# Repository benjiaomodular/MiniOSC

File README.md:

# MiniOSC
[![CC BY-SA 4.0][cc-by-sa-shield]][cc-by-sa]

## Schematics
**Version 2.1**

More info on my website: https://benjiaomodular.com/post/2024-09-20-miniosc-v2/

## PCBs
This project was sponsored by PCBWay. You can order the boards from them directly!
1. [MiniOSC v2.1 - Front panel](https://www.pcbway.com/project/shareproject/_1_of_2_MiniOSC_v2_1_Front_Panel_4b8c5ae8.html) 
2. [MiniOSC v2.1 - Main board](https://www.pcbway.com/project/shareproject/_2_of_2_MiniOSC_v2_1_Main_Board_2ed4e925.html)

You can also download my files from https://github.com/benjiaomodular/MiniOSC/blob/main/fabrication/

## Old versions

**Version 1.1**

More info on my website: https://benjiaomodular.com/post/2021-12-03-volt-per-octave-40106-vco/

## License

This work is licensed under a
[Creative Commons Attribution-ShareAlike 4.0 International License][cc-by-sa].

[![CC BY-SA 4.0][cc-by-sa-image]][cc-by-sa]

[cc-by-sa]: http://creativecommons.org/licenses/by-sa/4.0/
[cc-by-sa-image]: https://licensebuttons.net/l/by-sa/4.0/88x31.png
[cc-by-sa-shield]: https://img.shields.io/badge/License-CC%20BY--SA%204.0-lightgrey.svg

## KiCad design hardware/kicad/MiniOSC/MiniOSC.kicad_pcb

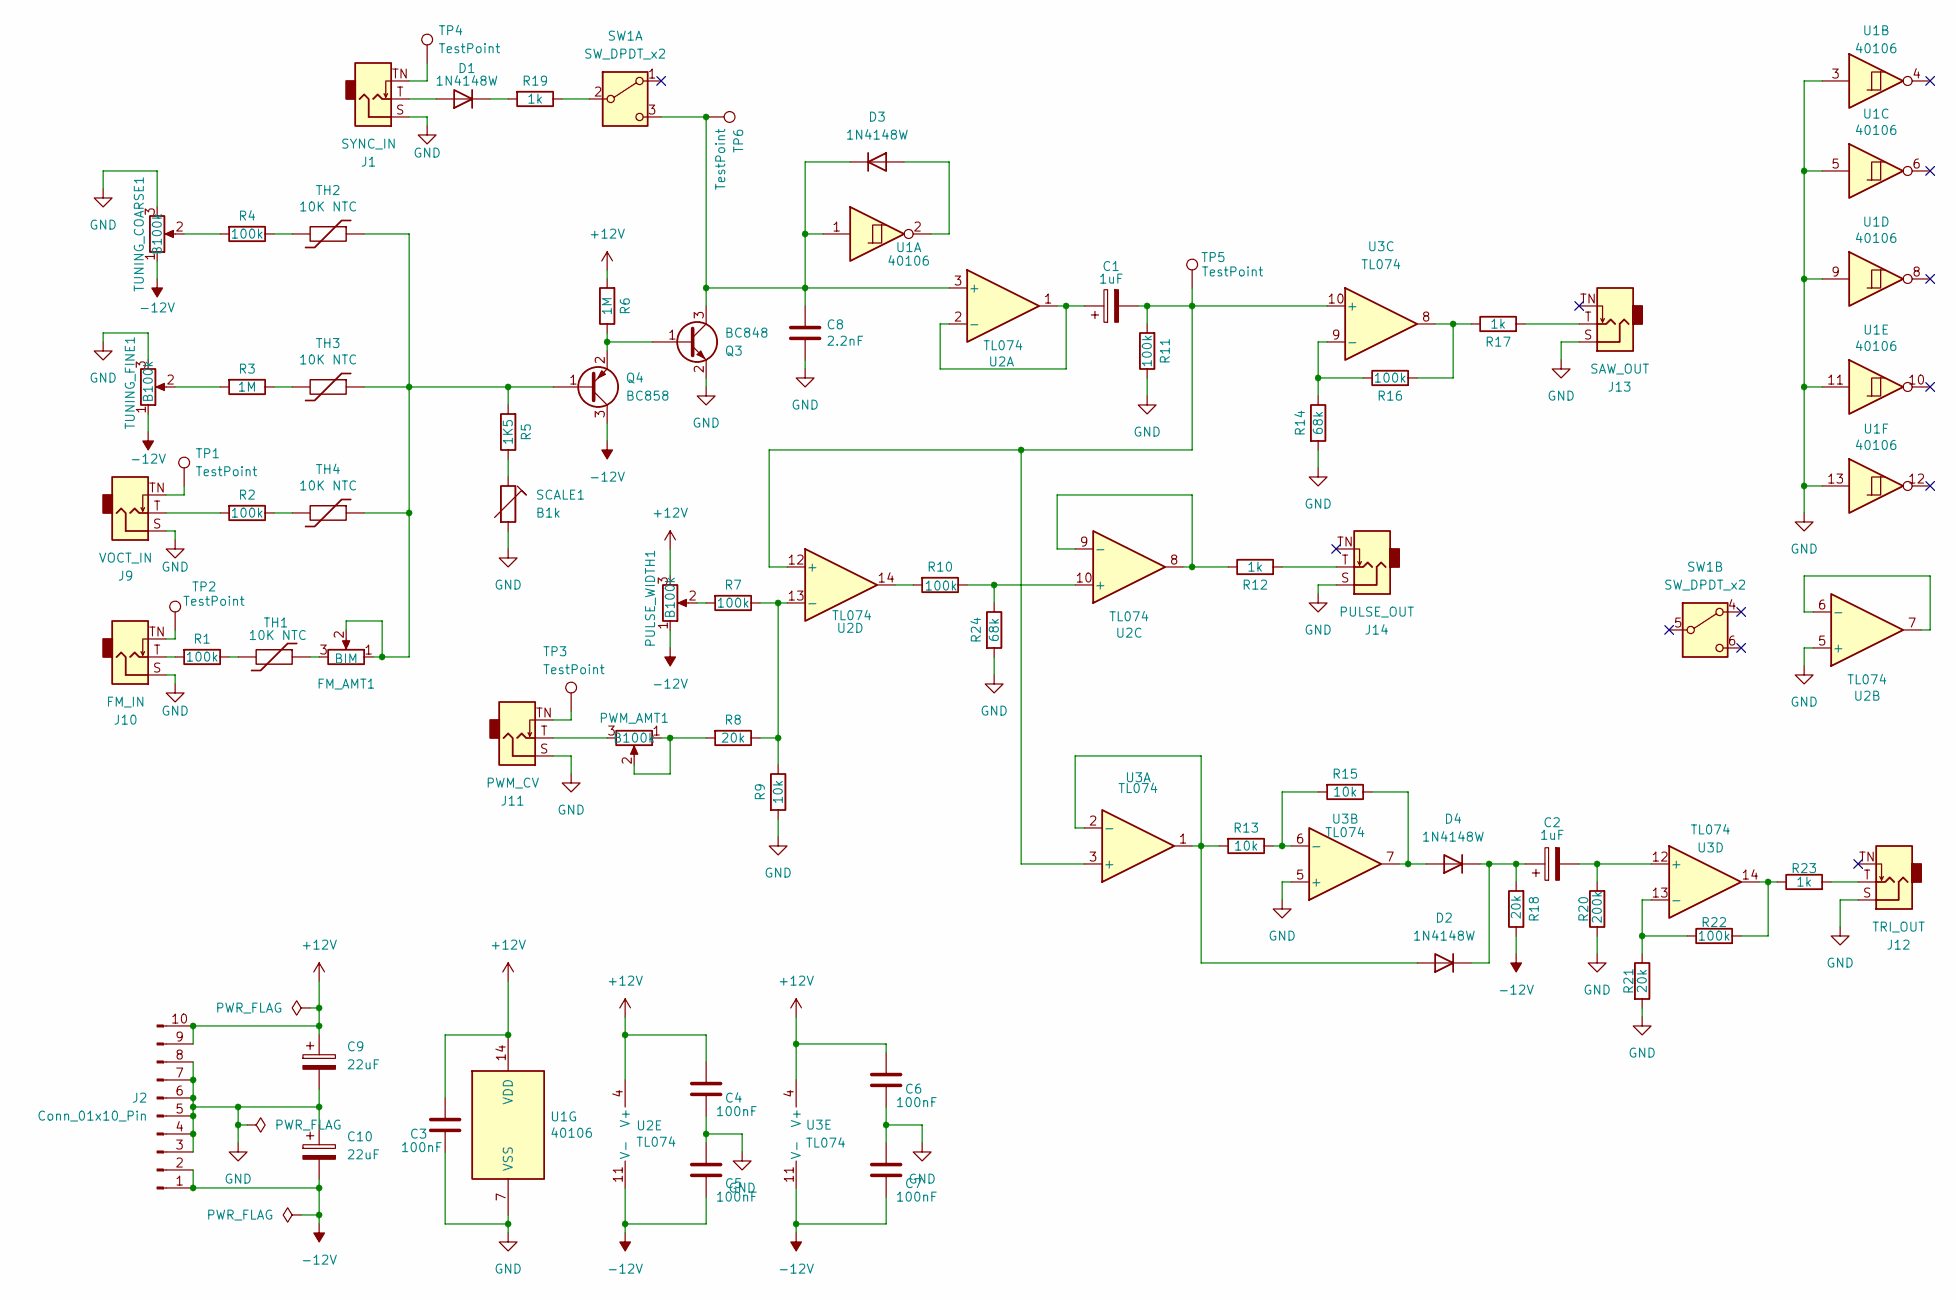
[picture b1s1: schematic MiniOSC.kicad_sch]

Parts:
C1, C2: 1uF; C_0805_2012Metric_Pad1.18x1.45mm_HandSolder; Part # UMK107AB7105KA-T
C3, C4, C5, C6, C7: 100nF; C_0805_2012Metric_Pad1.18x1.45mm_HandSolder; Part # CC0603JRX7R9BB104
C8: 2.2nF; C_0603_1608Metric_Pad1.08x0.95mm_HandSolder; Part # VJ0603Y681KXAAC
C9, C10: 22uF; CP_Elec_4x5.8; Part # EEE-FT1V220AR
D1, D2, D3, D4: 1N4148W; D_SOD-123; Part # 1N4148W_R2_00001
FM_AMT1: BIM; Potentiometer_RV09; Part # RV09AF-40-20K-B1M
J1: SYNC_IN; AudioJack_3.5mm; Part # PJ-3001F 3.5mm Mono Phone Jack
J2: Conn_01x10_Pin; Header_IDC2x05_NoArrow; Part # X9555WV-2X05-6TV01
J9: VOCT_IN; AudioJack_3.5mm; Part # PJ-3001F 3.5mm Mono Phone Jack
J10: FM_IN; AudioJack_3.5mm; Part # PJ-3001F 3.5mm Mono Phone Jack
J11: PWM_CV; AudioJack_3.5mm; Part # PJ-3001F 3.5mm Mono Phone Jack
J12: TRI_OUT; AudioJack_3.5mm; Part # PJ-3001F 3.5mm Mono Phone Jack
J13: SAW_OUT; AudioJack_3.5mm; Part # PJ-3001F 3.5mm Mono Phone Jack
J14: PULSE_OUT; AudioJack_3.5mm; Part # PJ-3001F 3.5mm Mono Phone Jack
PULSE_WIDTH1: B100k; Potentiometer_RV09; Part # RV9312NO-OS15A00-B100K-060
PWM_AMT1: B100k; Potentiometer_RV09; Part # RV09AF-40-20K-B100K
Q3: BC848; SOT-23; Part # BC848ALT1G
Q4: BC858; SOT-23; Part # BC858CLT3G
R1, R2, R4, R7, R10, R11, R16, R22: 100k; R_0603_1608Metric_Pad0.98x0.95mm_HandSolder; Part # RC0603FR-07100KL
R3, R6: 1M; R_0603_1608Metric_Pad0.98x0.95mm_HandSolder; Part # RC0603FR-071ML
R5: 1K5; R_0603_1608Metric_Pad0.98x0.95mm_HandSolder; Part # RC0603FR-071K5L
R8, R18: 20k; R_0603_1608Metric_Pad0.98x0.95mm_HandSolder; Part # RC0603FR-0720KL
R9, R13, R15: 10k; R_0603_1608Metric_Pad0.98x0.95mm_HandSolder; Part # AC0603FR-0710KL
R12, R17, R19, R23: 1k; R_0603_1608Metric_Pad0.98x0.95mm_HandSolder; Part # RC0603FR-071KL
R14, R24: 68k; R_0603_1608Metric_Pad0.98x0.95mm_HandSolder; Part # RC0603FR-0768KL
R20: 200k; R_0603_1608Metric_Pad0.98x0.95mm_HandSolder; Part # CR0603-FX-2003ELF
R21: 20k; R_0603_1608Metric_Pad0.98x0.95mm_HandSolder; Part # AC0603FR-0710KL
SCALE1: B1k; Potentiometer_Bourns_3296W_Vertical; Part # 3296W-1-102LF
SW1: SW_DPDT_x2; Button_KFC7x7; Part # PB-22E27-ROHS
TH1, TH2, TH3, TH4: 10K NTC; R_0805_2012Metric_Pad1.20x1.40mm_HandSolder; Part # NTCS0603E3103JLT
TP1, TP2, TP3, TP4, TP5, TP6: TestPoint; SolderWirePad_1x01_SMD_1x2mm
TUNING_COARSE1: B100k; Potentiometer_RV09; Part # RV9312NO-OS15A00-B100K-060
TUNING_FINE1: B100k; Potentiometer_RV09; Part # RV09AF-40-20K-B100K
U1: 40106; SOIC-14_3.9x8.7mm_P1.27mm; Part # CD40106BM96G4
U2, U3: TL074; SOIC-14_3.9x8.7mm_P1.27mm; Part # TL074ACDT

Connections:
+12V: C3.1, C4.1, C6.1, C9.1, J2.9, J2.10, PULSE_WIDTH1.3, R6.2, U1.14 (VDD), U2.4 (V+), U3.4 (V+)
-12V: C5.2, C7.2, C10.2, J2.1, J2.2, PULSE_WIDTH1.1, Q4.3 (C), R18.1, TUNING_COARSE1.1, TUNING_FINE1.1, U2.11 (V-), U3.11 (V-)
GND: C3.2, C4.2, C5.1, C6.2, C7.1, C8.2, C9.2, C10.1, J1.S, J2.3, J2.4, J2.5, J2.6, J2.7, J2.8, J9.S, J10.S, J11.S, J12.S, J13.S, J14.S, Q3.2 (E), R9.2, R11.1, R14.2, R20.1, R21.2, R24.2, SCALE1.2, TUNING_COARSE1.3, TUNING_FINE1.3, U1.3, U1.5, U1.7 (VSS), U1.9, U1.11, U1.13, U2.5 (+), U3.5 (+)
unnamed: D1.2 (A), J1.T
unnamed: D1.1 (K), R19.2
unnamed: D2.2 (A), R13.2, U3.1, U3.2 (-)
unnamed: C2.1, D2.1 (K), D4.1 (K), R18.2
unnamed: D3.2 (A), U1.2
unnamed: C8.1, D3.1 (K), Q3.3 (C), SW1.3 (C), TP6.1, U1.1, U2.3 (+)
unnamed: D4.2 (A), R15.1, U3.7
unnamed: FM_AMT1.3, TH1.1
unnamed: J1.TN, TP4.1
unnamed: J9.T, R2.2
unnamed: J9.TN, TP1.1
unnamed: J10.T, R1.2
unnamed: J10.TN, TP2.1
unnamed: J11.T, PWM_AMT1.3
unnamed: J11.TN, TP3.1
unnamed: J12.T, R23.2
unnamed: J13.T, R17.2
unnamed: J14.T, R12.2
unnamed: PULSE_WIDTH1.2, R7.2
unnamed: PWM_AMT1.1, PWM_AMT1.2, R8.2
unnamed: Q3.1 (B), Q4.2 (E), R6.1
unnamed: FM_AMT1.1, FM_AMT1.2, Q4.1 (B), R5.2, TH2.1, TH3.1, TH4.1
unnamed: R1.1, TH1.2
unnamed: R2.1, TH4.2
unnamed: R3.1, TH3.2
unnamed: R3.2, TUNING_FINE1.2
unnamed: R4.1, TH2.2
unnamed: R4.2, TUNING_COARSE1.2
unnamed: R5.1, SCALE1.1
unnamed: R10.2, U2.14
unnamed: R16.2, R17.1, U3.8
unnamed: R22.2, R23.1, U3.14
unnamed: R19.1, SW1.2 (B)
unnamed: C1.1, U2.1, U2.2 (-)
unnamed: U2.6 (-), U2.7
unnamed: R10.1, R24.1, U2.10 (+)
unnamed: R12.1, U2.8, U2.9 (-)
unnamed: C1.2, R11.2, TP5.1, U2.12 (+), U3.3 (+), U3.10 (+)
unnamed: R7.1, R8.1, R9.1, U2.13 (-)
unnamed: R13.1, R15.2, U3.6 (-)
unnamed: R14.1, R16.1, U3.9 (-)
unnamed: C2.2, R20.2, U3.12 (+)
unnamed: R21.1, R22.1, U3.13 (-)

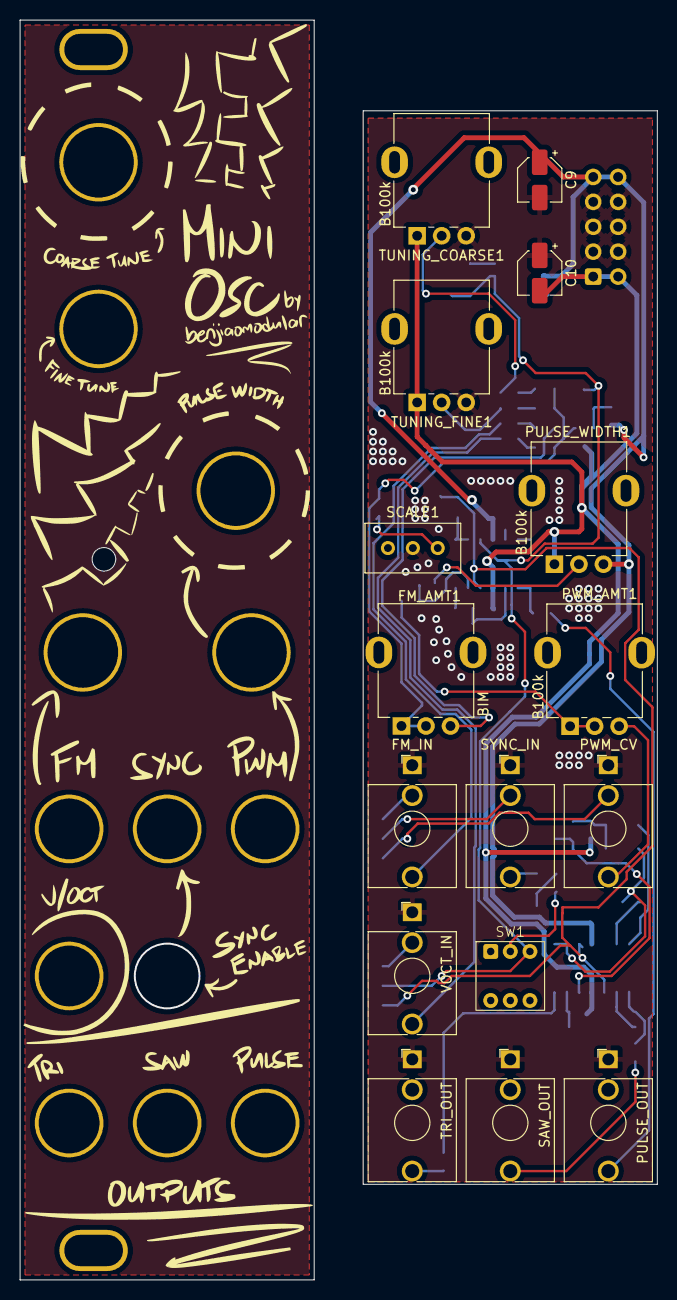
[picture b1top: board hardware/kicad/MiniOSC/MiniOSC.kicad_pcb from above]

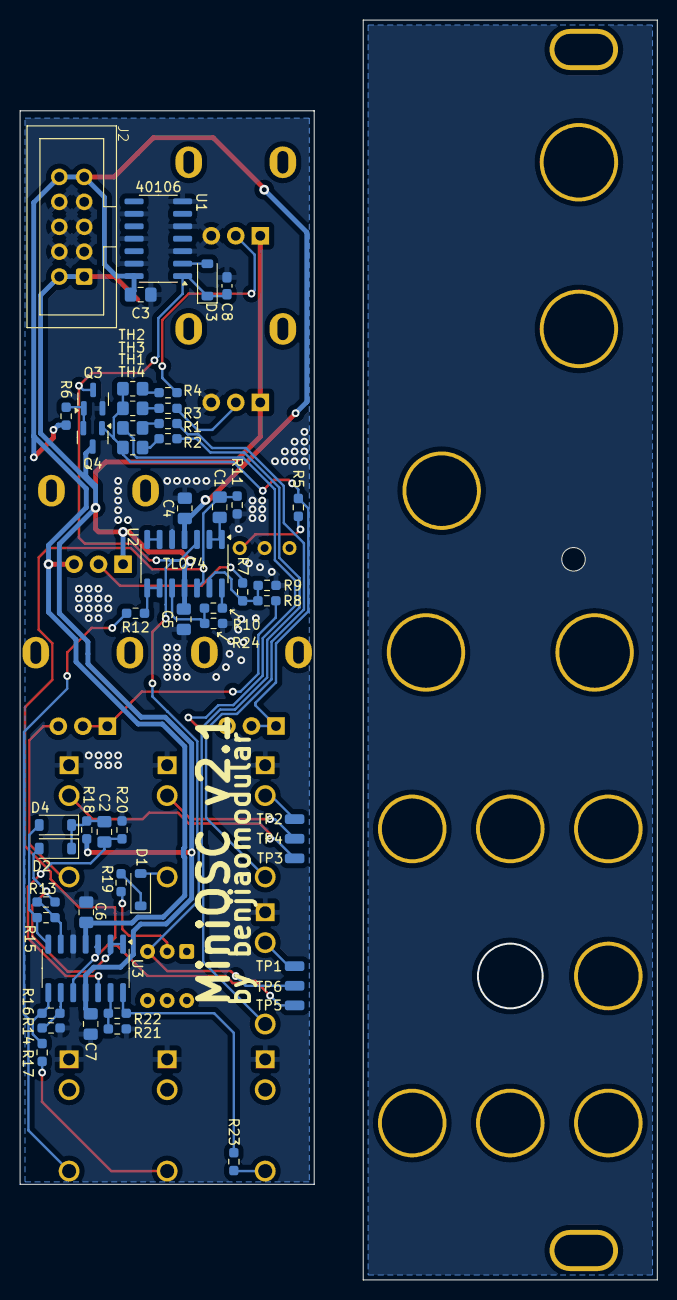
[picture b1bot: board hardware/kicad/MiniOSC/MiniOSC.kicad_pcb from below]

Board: 2 copper layers, 30.0 x 109.5 mm, 68 parts (52 on the bottom side), 46 nets.

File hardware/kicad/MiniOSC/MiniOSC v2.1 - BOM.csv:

"null","Sourced","Placed","References","Value","Footprint","URL","Manufacturer","Part #","Quantity"
1,"","","C3, C4, C5, C6, C7","100nF","C_0805_2012Metric_Pad1.18x1.45mm_HandSolder","https://mou.sr/4ekMsbM","YAGEO","CC0603JRX7R9BB104",5
2,"","","C1, C2","1uF","C_0805_2012Metric_Pad1.18x1.45mm_HandSolder","https://mou.sr/3XEhBl3","TAIYO YUDEN","UMK107AB7105KA-T",2
3,"","","C9, C10","22uF","CP_Elec_4x5.8","https://mou.sr/4ekMqRc","Panasonic","EEE-FT1V220AR",2
4,"","","C8","680pF","C_0603_1608Metric_Pad1.08x0.95mm_HandSolder","https://mou.sr/4goVMgC","Vishay / Vitramon","VJ0603Y681KXAAC",1
5,"","","R1, R2, R4, R7, R10, R11, R16, R22","100k","R_0603_1608Metric_Pad0.98x0.95mm_HandSolder","https://mou.sr/4el3qXS","YAGEO","RC0603FR-07100KL",8
6,"","","R12, R17, R19, R23","1k","R_0603_1608Metric_Pad0.98x0.95mm_HandSolder","https://mou.sr/3MKtPCB","YAGEO","RC0603FR-071KL",4
7,"","","R9, R13, R15","10k","R_0603_1608Metric_Pad0.98x0.95mm_HandSolder","https://mou.sr/3MINYsI","YAGEO","AC0603FR-0710KL",3
8,"","","R3, R6","1M","R_0603_1608Metric_Pad0.98x0.95mm_HandSolder","https://mou.sr/3Znalvs","YAGEO","RC0603FR-071ML",2
9,"","","R8, R18","20k","R_0603_1608Metric_Pad0.98x0.95mm_HandSolder","https://mou.sr/3z5b9KJ","YAGEO","RC0603FR-0720KL",2
10,"","","R14, R24","68k","R_0603_1608Metric_Pad0.98x0.95mm_HandSolder","https://mou.sr/3ToI2ZD","YAGEO","RC0603FR-0768KL",2
11,"","","R5","1K5","R_0603_1608Metric_Pad0.98x0.95mm_HandSolder","https://mou.sr/3zoxpz1","YAGEO"," RC0603FR-071K5L",1
12,"","","R20","200k","R_0603_1608Metric_Pad0.98x0.95mm_HandSolder","https://mou.sr/3XFl5np","Bourns","CR0603-FX-2003ELF",1
13,"","","R21","20k","R_0603_1608Metric_Pad0.98x0.95mm_HandSolder","https://mou.sr/3MINYsI","YAGEO","AC0603FR-0710KL",1
14,"","","D1, D2, D3, D4","1N4148W","D_SOD-123","https://mou.sr/3XEhTbD","Panjit"," 1N4148W_R2_00001",4
15,"","","U2, U3","TL074","SOIC-14_3.9x8.7mm_P1.27mm","https://mou.sr/3z6QVAe","STMicroelectronics","TL074ACDT",2
16,"","","U1",40106,"SOIC-14_3.9x8.7mm_P1.27mm","https://mou.sr/47m5xIo","Texas Instruments","CD40106BM96G4",1
17,"","","SW1","SW_DPDT_x2","Button_KFC7x7","https://www.taydaelectronics.com/push-button-switch-dc-30v-0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","DAIER"," PB-22E27-ROHS",1
18,"","","TH1, TH2, TH3, TH4","10K NTC","R_0805_2012Metric_Pad1.20x1.40mm_HandSolder","https://mou.sr/4el3hDO","Vishay / BC Components","NTCS0603E3103JLT",4
19,"","","PULSE_WIDTH1, TUNING_COARSE1","B100k","Potentiometer_RV09","https://www.taydaelectronics.com/tayda-100k-ohm-linear-taper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","Tayda Electronics","RV9312NO-OS15A00-B100K-060",2
20,"","","PWM_AMT1, TUNING_FINE1","B100k","Potentiometer_RV09","https://www.taydaelectronics.com/100k-ohm-linear-taper-poten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","ALPHA","RV09AF-40-20K-B100K",2
21,"","","FM_AMT1","BIM","Potentiometer_RV09","https://www.taydaelectronics.com/1m-ohm-linear-taper-potenti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","ALPHA","RV09AF-40-20K-B1M",1
22,"","","Q3","BC848","SOT-23","https://mou.sr/3B2EAO3","onsemi","BC848ALT1G",1
23,"","","Q4","BC858","SOT-23","https://mou.sr/3ZkYkq0","onsemi","BC858CLT3G",1
24,"","","SCALE1","B1k","Potentiometer_Bourns_3296W_Vertical","https://www.taydaelectronics.com/1k-ohm-trimmer-potentiomete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","ALPHA","3296W-1-102LF",1
25,"","","J1","SYNC_IN","AudioJack_3.5mm","https://www.taydaelectronics.com/pj-3001f-3-5-mm-mono-phone-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","Tayda Electronics","PJ-3001F 3.5mm Mono Phone Jack",1
26,"","","J2","Conn_01x10_Pin","Header_IDC2x05_NoArrow","","XKB Connectivity","X9555WV-2X05-6TV01",1
27,"","","J9","VOCT_IN","AudioJack_3.5mm","https://www.taydaelectronics.com/pj-3001f-3-5-mm-mono-phone-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","Tayda Electronics","PJ-3001F 3.5mm Mono Phone Jack",1
28,"","","J10","FM_IN","AudioJack_3.5mm","https://www.taydaelectronics.com/pj-3001f-3-5-mm-mono-phone-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","Tayda Electronics","PJ-3001F 3.5mm Mono Phone Jack",1
29,"","","J11","PWM_CV","AudioJack_3.5mm","https://www.taydaelectronics.com/pj-3001f-3-5-mm-mono-phone-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","Tayda Electronics","PJ-3001F 3.5mm Mono Phone Jack",1
30,"","","J12","TRI_OUT","AudioJack_3.5mm","https://www.taydaelectronics.com/pj-3001f-3-5-mm-mono-phone-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","Tayda Electronics","PJ-3001F 3.5mm Mono Phone Jack",1
31,"","","J13","SAW_OUT","AudioJack_3.5mm","https://www.taydaelectronics.com/pj-3001f-3-5-mm-mono-phone-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","Tayda Electronics","PJ-3001F 3.5mm Mono Phone Jack",1
32,"","","J14","PULSE_OUT","AudioJack_3.5mm","https://www.taydaelectronics.com/pj-3001f-3-5-mm-mono-phone-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","Tayda Electronics","PJ-3001F 3.5mm Mono Phone Jack",1

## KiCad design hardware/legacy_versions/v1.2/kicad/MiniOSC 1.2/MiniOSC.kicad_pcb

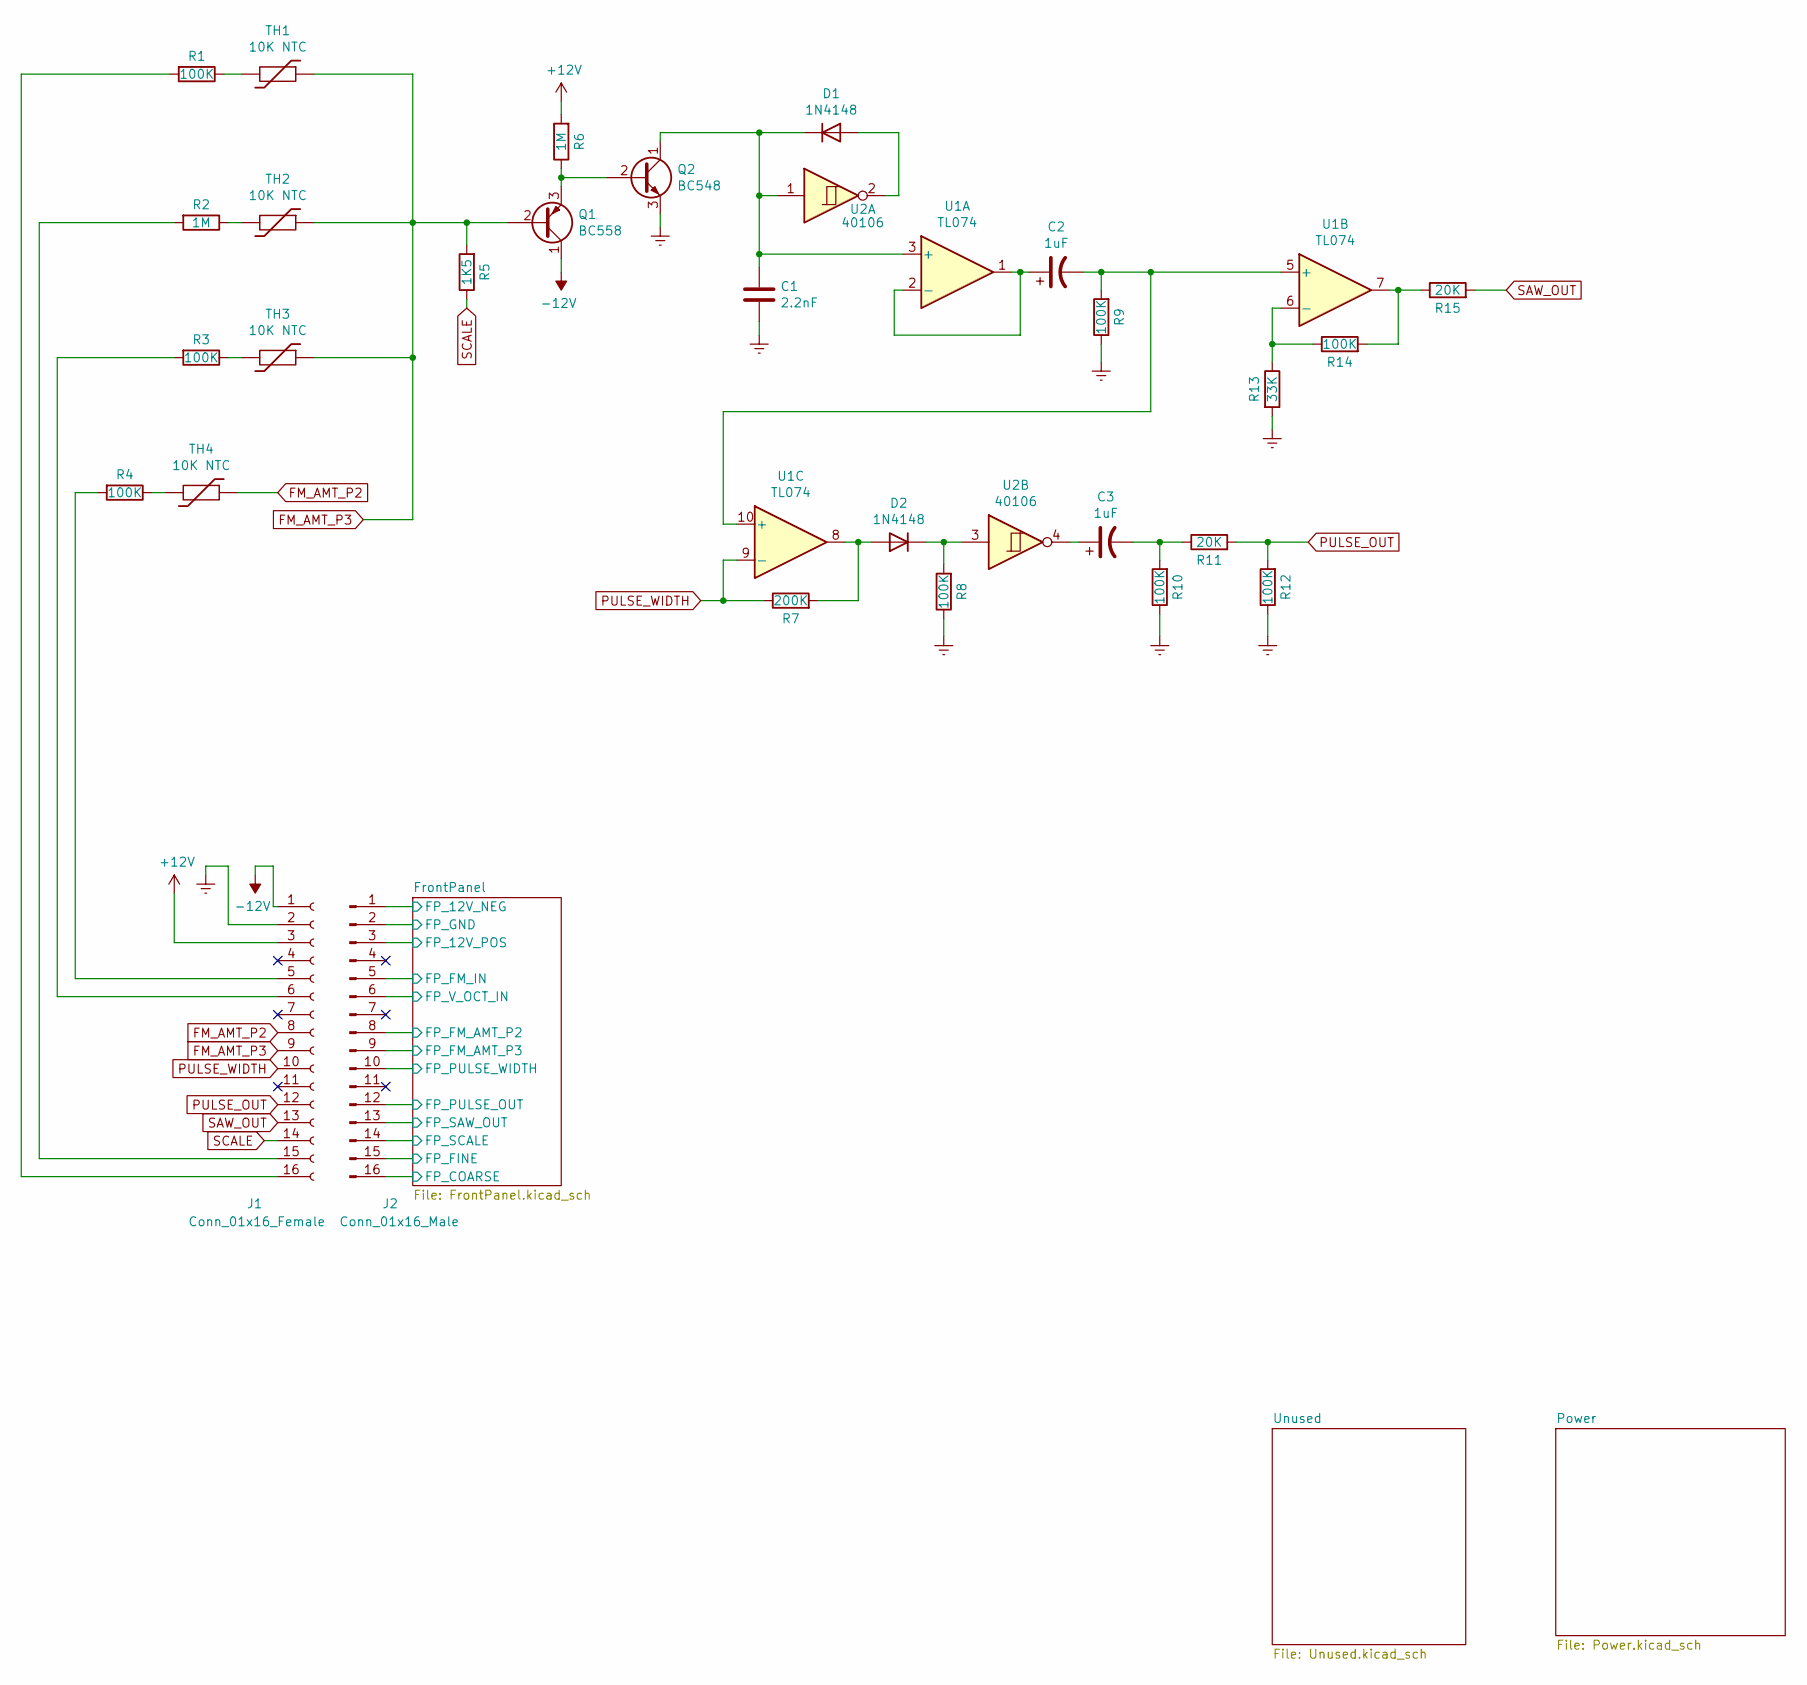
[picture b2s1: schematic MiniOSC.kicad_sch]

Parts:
C1: 2.2nF; C_Rect_L7.2mm_W2.5mm_P5.00mm_FKS2_FKP2_MKS2_MKP2
C2, C3: 1uF; CP_Radial_D5.0mm_P2.50mm
D1, D2: 1N4148; D_DO-35_SOD27_P7.62mm_Horizontal
J1: Conn_01x16_Female; PinHeader_1x16_P2.54mm_Vertical
J2: Conn_01x16_Male; PinHeader_1x16_P2.54mm_Vertical
Q1: BC558; TO-92_Inline
Q2: BC548; TO-92_Inline
R1, R3, R4, R8, R9, R10, R12, R14: 100K; R_Axial_DIN0207_L6.3mm_D2.5mm_P7.62mm_Horizontal
R2, R6: 1M; R_Axial_DIN0207_L6.3mm_D2.5mm_P7.62mm_Horizontal
R5: 1K5; R_Axial_DIN0207_L6.3mm_D2.5mm_P7.62mm_Horizontal
R7: 200K; R_Axial_DIN0207_L6.3mm_D2.5mm_P7.62mm_Horizontal
R11, R15: 20K; R_Axial_DIN0207_L6.3mm_D2.5mm_P7.62mm_Horizontal
R13: 33K; R_Axial_DIN0207_L6.3mm_D2.5mm_P7.62mm_Horizontal
TH1, TH2, TH3, TH4: 10K NTC; C_Disc_D3.8mm_W2.6mm_P2.50mm
U1: TL074; DIP-14_W7.62mm_Socket
U2: 40106; DIP-14_W7.62mm_Socket

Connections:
+12V: J1.3, R6.2; also elsewhere on the board
-12V: J1.1, Q1.1 (C); also elsewhere on the board
/FrontPanel/FP_12V_POS: J2.3; also elsewhere on the board
/FrontPanel/FP_COARSE: J2.16; also elsewhere on the board
/FrontPanel/FP_FINE: J2.15; also elsewhere on the board
/FrontPanel/FP_FM_AMT_P2: J2.8; also elsewhere on the board
/FrontPanel/FP_FM_AMT_P3: J2.9; also elsewhere on the board
/FrontPanel/FP_FM_IN: J2.5; also elsewhere on the board
/FrontPanel/FP_PULSE_OUT: J2.12; also elsewhere on the board
/FrontPanel/FP_PULSE_WIDTH: J2.10; also elsewhere on the board
/FrontPanel/FP_SAW_OUT: J2.13; also elsewhere on the board
/FrontPanel/FP_SCALE: J2.14; also elsewhere on the board
/FrontPanel/FP_V_OCT_IN: J2.6; also elsewhere on the board
Earth: C1.2, J1.2, Q2.3 (E), R8.1, R9.1, R10.1, R12.1, R13.2; also elsewhere on the board
FM_AMT_P2: J1.8, TH4.1
FM_AMT_P3: J1.9, Q1.2 (B), R5.2, TH1.1, TH2.1, TH3.1
FP_12V_NEG: J2.1; also elsewhere on the board
GND1: J2.2; also elsewhere on the board
unnamed: C1.1, D1.1 (K), Q2.1 (C), U1.3 (+), U2.1
unnamed: C2.1, U1.1, U1.2 (-)
unnamed: C2.2, R9.2, U1.5 (+), U1.10 (+)
unnamed: C3.1, U2.4
unnamed: C3.2, R10.2, R11.1
unnamed: D1.2 (A), U2.2
unnamed: D2.1 (K), R8.2, U2.3
unnamed: D2.2 (A), R7.2, U1.8
unnamed: J1.5, R4.2
unnamed: J1.6, R3.2
unnamed: J1.15, R2.2
unnamed: J1.16, R1.2
unnamed: Q1.3 (E), Q2.2 (B), R6.1
unnamed: R1.1, TH1.2
unnamed: R2.1, TH2.2
unnamed: R3.1, TH3.2
unnamed: R4.1, TH4.2
unnamed: R13.1, R14.1, U1.6 (-)
unnamed: R14.2, R15.1, U1.7
PULSE_OUT: J1.12, R11.2, R12.2
PULSE_WIDTH: J1.10, R7.1, U1.9 (-)
SAW_OUT: J1.13, R15.2
SCALE: J1.14, R5.1

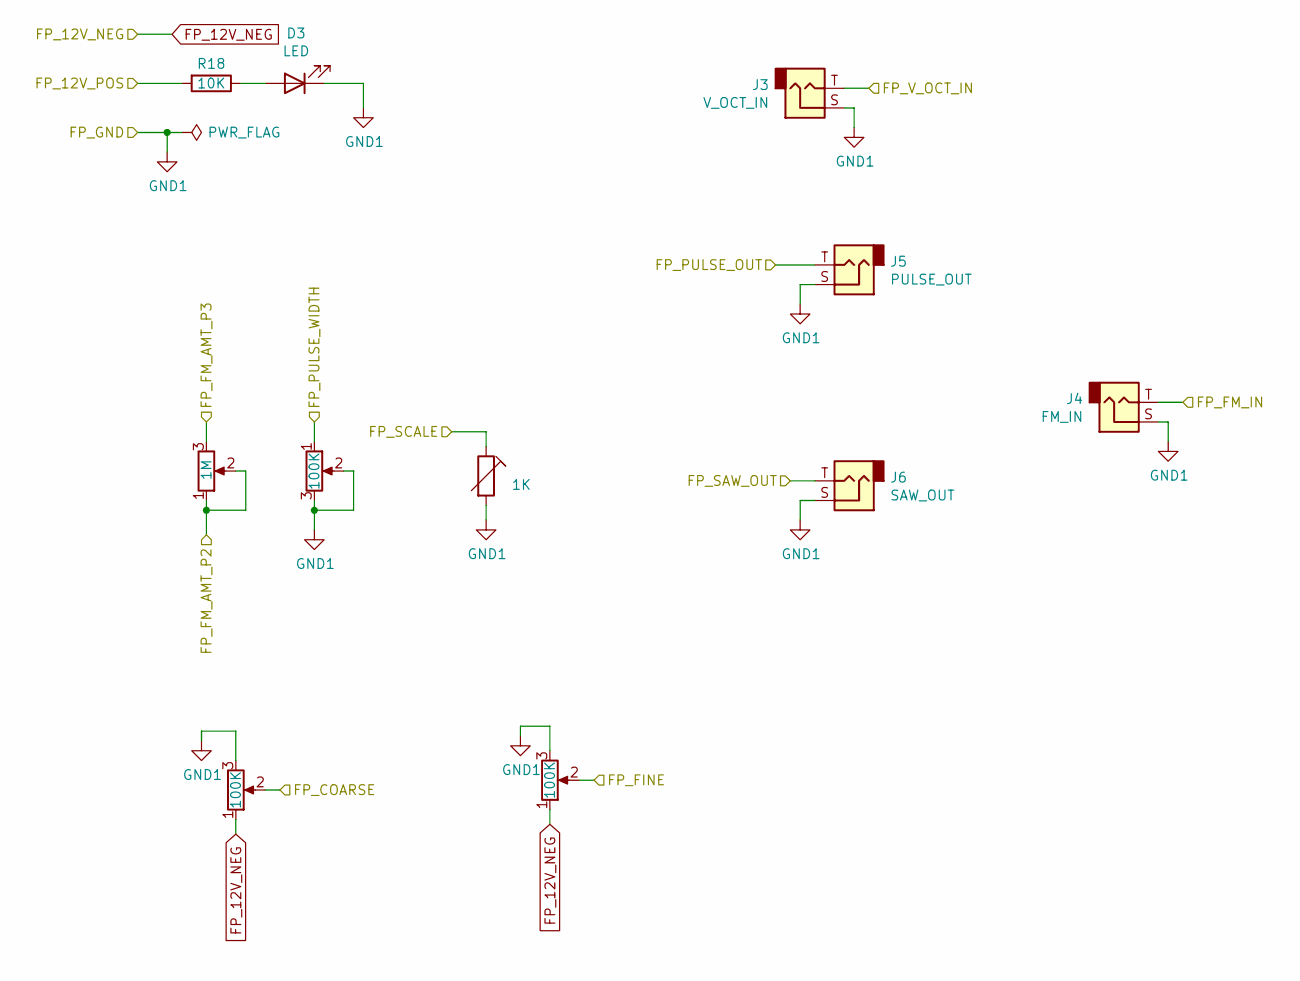
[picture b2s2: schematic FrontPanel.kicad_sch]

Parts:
D3: LED; LED_D3.0mm
J3: V_OCT_IN; Jack_3.5mm_QingPu_WQP-PJ398SM_Vertical_CircularHoles
J4: FM_IN; Jack_3.5mm_QingPu_WQP-PJ398SM_Vertical_CircularHoles
J5: PULSE_OUT; Jack_3.5mm_QingPu_WQP-PJ398SM_Vertical_CircularHoles
J6: SAW_OUT; Jack_3.5mm_QingPu_WQP-PJ398SM_Vertical_CircularHoles
R18: 10K; R_Axial_DIN0207_L6.3mm_D2.5mm_P7.62mm_Horizontal

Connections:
/FrontPanel/FP_12V_POS: R18.2; also elsewhere on the board
/FrontPanel/FP_FM_IN: J4.T; also elsewhere on the board
/FrontPanel/FP_PULSE_OUT: J5.T; also elsewhere on the board
/FrontPanel/FP_SAW_OUT: J6.T; also elsewhere on the board
/FrontPanel/FP_V_OCT_IN: J3.T; also elsewhere on the board
GND1: D3.1 (K), J3.S, J4.S, J5.S, J6.S; also elsewhere on the board
unnamed: D3.2 (A), R18.1

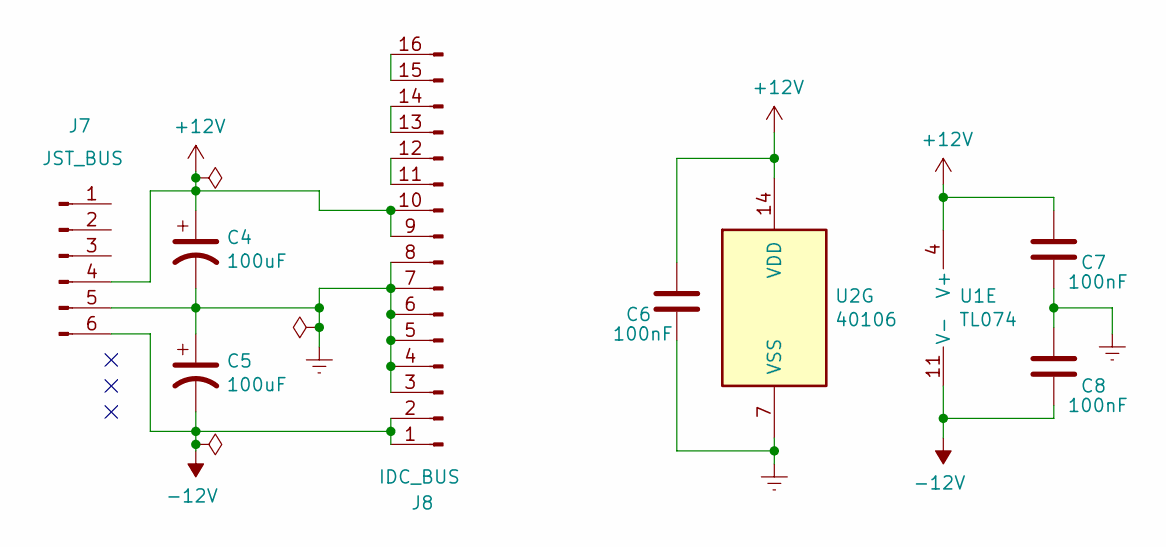
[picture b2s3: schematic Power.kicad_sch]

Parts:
C4, C5: 100uF; CP_Radial_D5.0mm_P2.50mm
C6, C7, C8: 100nF; C_Rect_L7.2mm_W2.5mm_P5.00mm_FKS2_FKP2_MKS2_MKP2
J7: JST_BUS; JST_XH_B6B-XH-A_1x06_P2.50mm_Vertical
J8: IDC_BUS; IDC-Header_2x08_P2.54mm_Vertical
U1: TL074; DIP-14_W7.62mm_Socket
U2: 40106; DIP-14_W7.62mm_Socket

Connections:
+12V: C4.1, C6.1, C7.1, J7.4, J8.9, J8.10, U1.4 (V+), U2.14 (VDD); also elsewhere on the board
-12V: C5.2, C8.2, J7.6, J8.1, J8.2, U1.11 (V-); also elsewhere on the board
Earth: C4.2, C5.1, C6.2, C7.2, C8.1, J7.5, J8.3, J8.4, J8.5, J8.6, J8.7, J8.8, U2.7 (VSS); also elsewhere on the board
unnamed: J8.11, J8.12
unnamed: J8.13, J8.14
unnamed: J8.15, J8.16

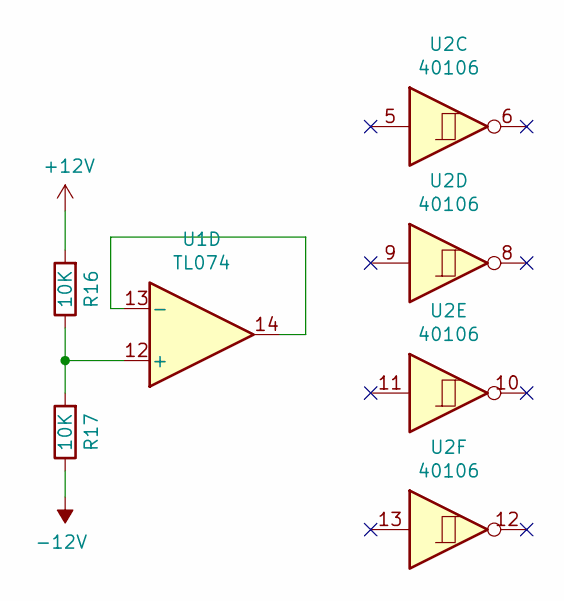
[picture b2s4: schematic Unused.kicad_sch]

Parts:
R16, R17: 10K; R_Axial_DIN0207_L6.3mm_D2.5mm_P7.62mm_Horizontal
U1: TL074; DIP-14_W7.62mm_Socket
U2: 40106

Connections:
+12V: R16.2; also elsewhere on the board
-12V: R17.1; also elsewhere on the board
unnamed: R16.1, R17.2, U1.12 (+)
unnamed: U1.13 (-), U1.14

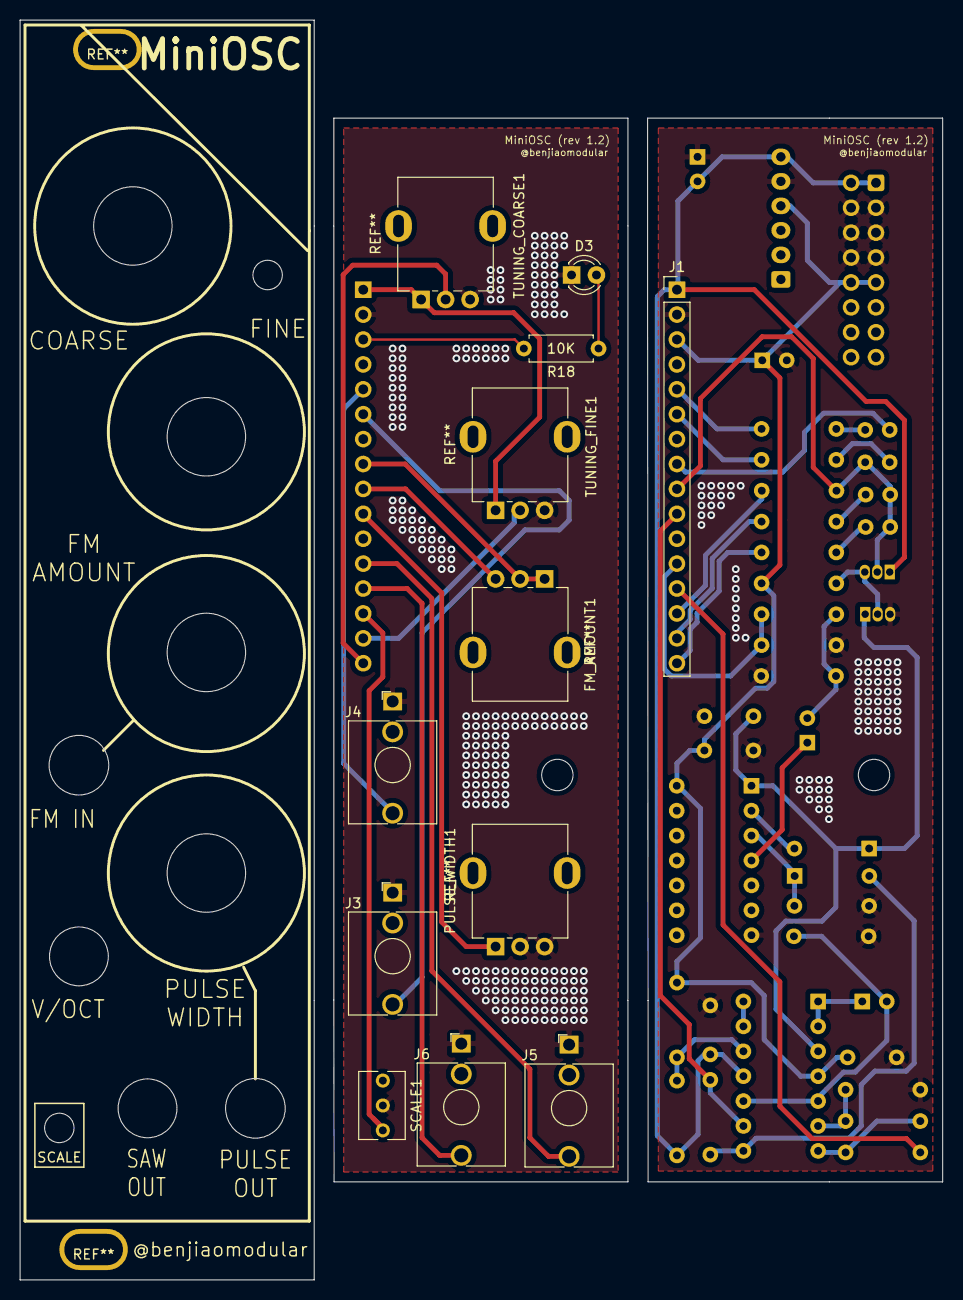
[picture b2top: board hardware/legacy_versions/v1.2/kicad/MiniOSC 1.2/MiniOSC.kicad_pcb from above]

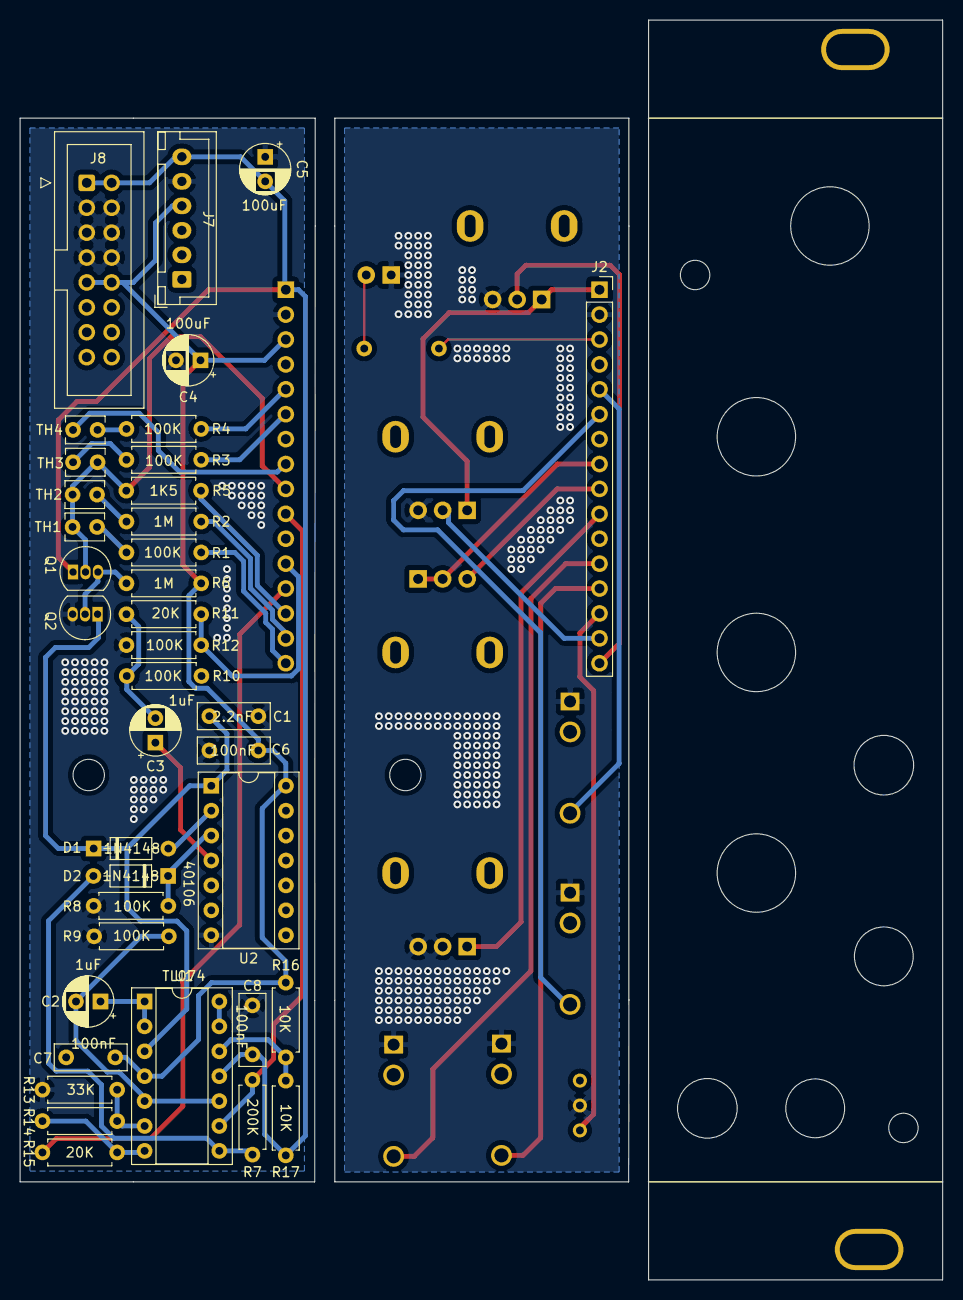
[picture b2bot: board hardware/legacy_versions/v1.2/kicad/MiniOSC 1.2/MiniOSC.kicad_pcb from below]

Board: 2 copper layers, 94.1 x 128.5 mm, 50 parts (38 on the bottom side), 47 nets.

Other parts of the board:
FM_AMOUNT1: 1M; Potentiometer_RV09
PULSE_WIDTH1: 100K; Potentiometer_RV09
SCALE1: 1K; Potentiometer_Bourns_3266Y_Vertical
TUNING_COARSE1: 100K; Potentiometer_RV09
TUNING_FINE1: 100K; Potentiometer_RV09

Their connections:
/FrontPanel/FP_COARSE: TUNING_COARSE1.2; also elsewhere on the board
/FrontPanel/FP_FINE: TUNING_FINE1.2; also elsewhere on the board
/FrontPanel/FP_FM_AMT_P2: FM_AMOUNT1.1, FM_AMOUNT1.2; also elsewhere on the board
/FrontPanel/FP_FM_AMT_P3: FM_AMOUNT1.3; also elsewhere on the board
/FrontPanel/FP_PULSE_WIDTH: PULSE_WIDTH1.1; also elsewhere on the board
/FrontPanel/FP_SCALE: SCALE1.1; also elsewhere on the board
FP_12V_NEG: TUNING_COARSE1.1, TUNING_FINE1.1; also elsewhere on the board
GND1: PULSE_WIDTH1.2, PULSE_WIDTH1.3, SCALE1.2, TUNING_COARSE1.3, TUNING_FINE1.3; also elsewhere on the board

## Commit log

2021-11-08 Added gerber files
2021-11-08 reorganized files
2021-11-08 updated license
2021-11-08 Updated license to MIT
2021-11-08 renamed readme
2021-11-08 added initial readme
2021-12-03 Added rev 1.1
2021-12-03 Added BOM files
2021-12-04 Rename MiniOSC.csv to MiniOSC - BOM.csv
2021-12-22 Added simplified schem
2022-01-05 Added fist 1.2 commit
2022-01-07 Transfered labels to solder mask
2022-01-17 Updated labels
2022-05-12 Added v1.2
2022-05-12 Added v1.2 docs
2022-08-05 Added updated build files for 1.2
2024-04-12 added new branch for v2
2024-09-06 updated symbols and grid to kicad 8
2024-09-06 Reorganized files. Updated license to CC-BY-SA
2024-09-11 v2.0 PCB
2024-09-24 Added v2.1
2024-09-25 Added fab files for v2.1
2024-09-25 Updated R21 value
2024-09-28 Removed reference label on frontpanel
2024-09-29 Updated changelog
2024-10-07 Fixed typo on R14 value
2024-10-11 Added manufacture parts numbers to BOM
2024-10-14 Added links to PCBWay, updated bom
2024-10-14 Added link to website
2024-10-14 updated bom
2024-10-27 Fixed v2.1 BOM
2024-10-29 Test PCB for v2.1.1 with throughole parts
